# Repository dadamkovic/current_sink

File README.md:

The design is intended to be a programmable current sink controllable manually using an encoder or over USB interface.
It ECU includes:
- 2 parallel separately controlled MOSFETs
- starburst type LCD display with 8 segments + driver IC
- symmetrical power rails +/- 5V
- USB optical isolation protection
- 2 channel DAC
- current monitoring
- optional 'PID' feedback control loop realized using cascaded op-amps 

Current state - HW is finished and a prototype was produced. SW library for control of the display is ready and included in the SW files.

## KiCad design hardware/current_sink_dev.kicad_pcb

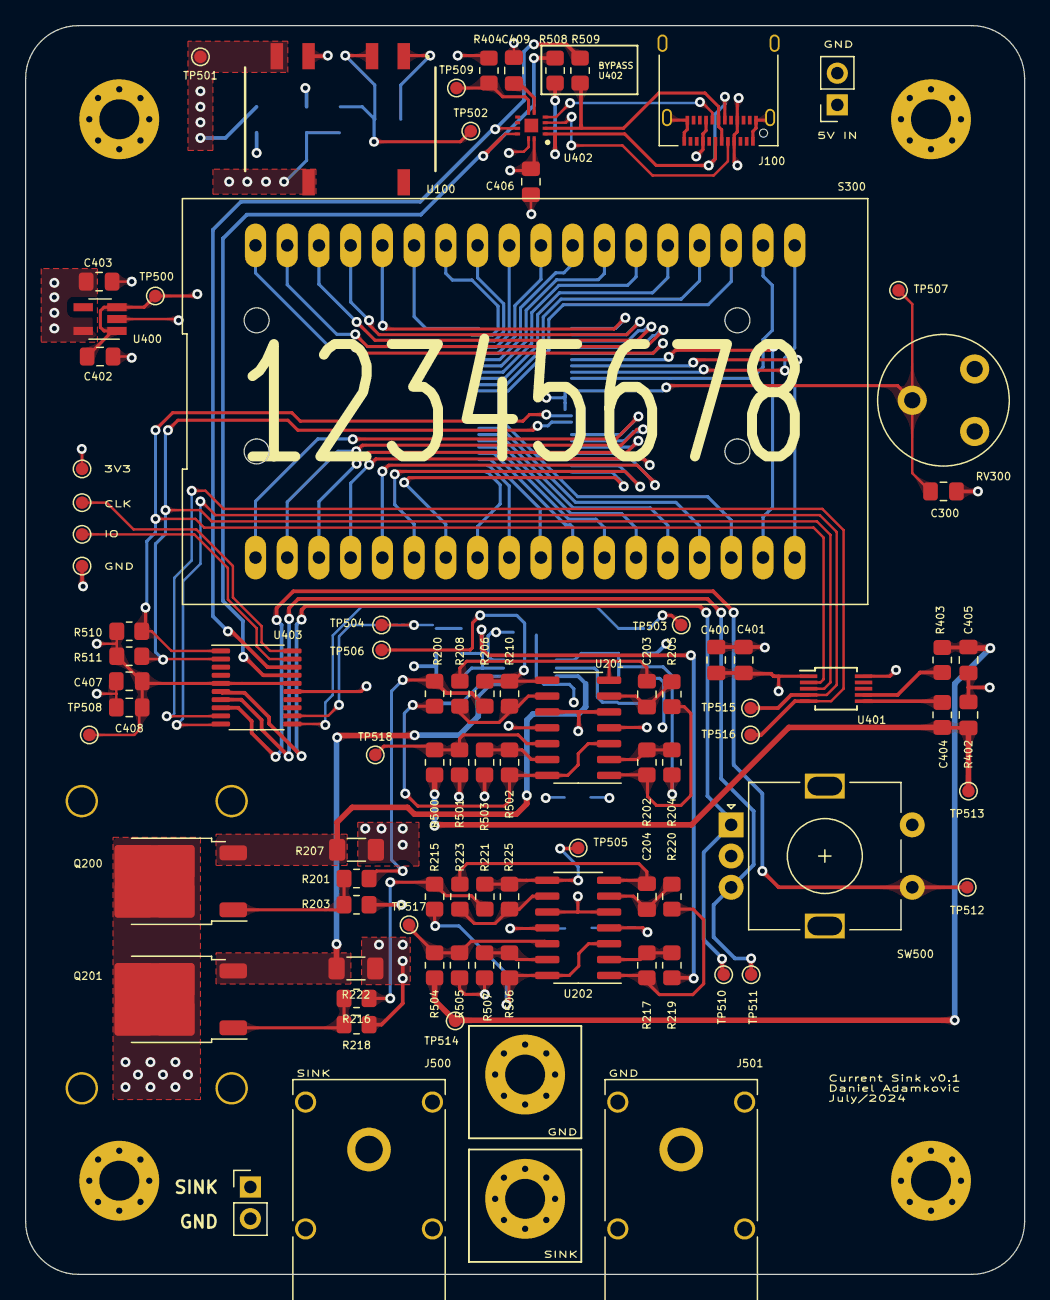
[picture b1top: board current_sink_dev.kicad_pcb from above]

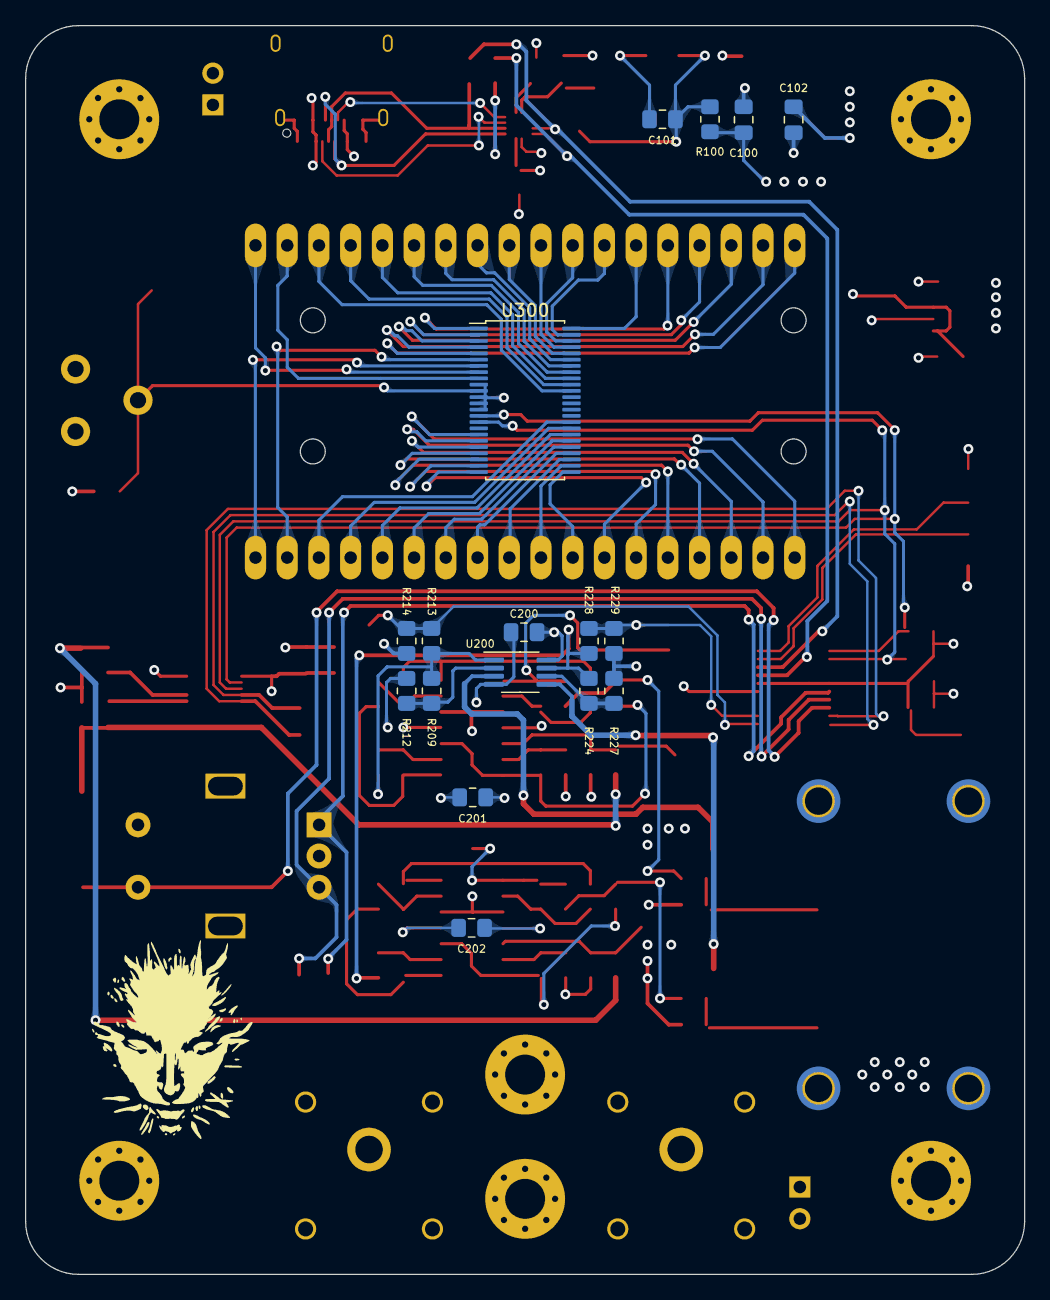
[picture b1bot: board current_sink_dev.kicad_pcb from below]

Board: 4 copper layers, 80.0 x 100.0 mm, 115 parts (21 on the bottom side), 94 nets.

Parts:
C100, C101, C102: 4.7u; C_0805_2012Metric_Pad1.18x1.45mm_HandSolder
C200, C201, C202: ?; C_0805_2012Metric_Pad1.18x1.45mm_HandSolder
C203, C204, C300, C402, C403, C406, C407, C408: 1u; C_0805_2012Metric_Pad1.18x1.45mm_HandSolder
C400, C404, C405, C409: 0.1u; C_0805_2012Metric_Pad1.18x1.45mm_HandSolder
C401: 10u; C_0805_2012Metric_Pad1.18x1.45mm_HandSolder
H500, H501, H502, H503, H504, H505: MountingHole_3.2mm_M3_Pad_Via
H506, H507, H508, H509: MountingHole_2.2mm_M2_ISO7380_Pad_TopOnly
J100: USB_C_Receptacle_USB2.0; USB_C_Receptacle_Amphenol_12401610E4-2A
J500, J501: Conn_01x01_Socket; Banana_Cliff_FCR7350x_S16N-PC_Horizontal
J502: PinHeader_1x02_P2.54mm_Vertical
J503: 5V_IN; PinSocket_1x02_P2.54mm_Vertical
Q200, Q201: TK7S10N1Z; TO-252-2
R100, R500, R501, R504, R505, R508, R509: 0R; R_0805_2012Metric_Pad1.20x1.40mm_HandSolder
R200, R206, R215, R221: 0; R_0805_2012Metric_Pad1.20x1.40mm_HandSolder
R201, R212, R213, R214, R216, R227, R228, R229: 100; R_0805_2012Metric_Pad1.20x1.40mm_HandSolder
R202, R204, R205, R208, R210, R217, R219, R220, R223, R225, R402, R403, R404: 10k; R_0805_2012Metric_Pad1.20x1.40mm_HandSolder
R203, R218: 1k; R_0805_2012Metric_Pad1.20x1.40mm_HandSolder
R207, R222: 100m; R_1206_3216Metric_Pad1.30x1.75mm_HandSolder
R209, R224: 1.9k; R_0805_2012Metric_Pad1.20x1.40mm_HandSolder
R502, R503, R506, R507: R_Small; R_0805_2012Metric_Pad1.20x1.40mm_HandSolder
R510, R511: ?; R_0805_2012Metric_Pad1.20x1.40mm_HandSolder
RV300: PT10LV05; Potentiometer_Piher_PT-10-V05_Vertical
S300: VIM-878-DP-RC-S-LV; VIM878DPRCSLV
SW500: RotaryEncoder_Switch; RotaryEncoder_Alps_EC11E-Switch_Vertical_H20mm
TP500, TP501, TP502, TP503, TP504, TP505, TP506, TP507, TP508, TP509, TP510, TP511, TP512, TP513, TP514, TP515, TP516, TP517, TP518: TestPoint_Pad_D1.0mm
TP519: 3V3; TestPoint_Pad_D1.0mm
TP520: SWDIO; TestPoint_Pad_D1.0mm
TP521: SWDCLK; TestPoint_Pad_D1.0mm
TP522: GND; TestPoint_Pad_D1.0mm
U100: PDSE1-S5-D5-M-TR; PDS1-M
U200: AD8602; MSOP-8_3x3mm_P0.65mm
U201, U202: ADTL084; SOIC-14_3.9x8.7mm_P1.27mm
U300: BU9797A; TSSOP-48_6.1x12.5mm_P0.5mm
U400: MIC5504-1.2YM5; SOT-23-5_HandSoldering
U401: MCP4728; MSOP-10_3x3mm_P0.5mm
U402: DPO2036; UQFN2020-12
U403: STM32F042F6Px; TSSOP-20_4.4x6.5mm_P0.65mm

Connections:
3V3_SUPPLY_G: C400.1, C401.1, C403.1, C406.1, C407.1, C408.1, R404.1, R510.1, R511.1, RV300.3, TP508.1, TP519.1, U400.5 (VOUT), U401.1 (VDD), U402.12 (VSYS), U403.5 (VDDA), U403.16 (VDD)
5V0_SUPPLY_G: C100.1, C200.2, C201.2, C202.2, C402.1, R100.2, TP500.1, U100.7 (+Vout), U200.8 (V+), U201.4 (V+), U202.4 (V+), U400.1 (VIN), U400.3 (EN)
-5V0_SUPPLY_G: C102.2, C200.1, C201.1, C202.1, TP501.1, U100.5 (-Vout), U200.4 (V-), U201.11 (V-), U202.11 (V-)
/LCD_screen/COM0_dig_l: S300.17 (COM0), U300.6 (COM0)
/LCD_screen/COM1_dig_l: S300.18 (COM1), U300.7 (COM1)
/LCD_screen/COM2_dig_l: S300.19 (COM2), U300.8 (COM2)
/LCD_screen/COM3_dig_l: S300.20 (COM3), U300.9 (COM3)
/LCD_screen/disp1_dig_l: S300.1 (PIN1), U300.18 (SEG0)
/LCD_screen/disp2_dig_l: S300.2 (PIN2), U300.19 (SEG1)
/LCD_screen/disp3_dig_l: S300.3 (PIN3), U300.20 (SEG2)
/LCD_screen/disp4_dig_l: S300.4 (PIN4), U300.21 (SEG3)
/LCD_screen/disp5_dig_l: S300.5 (PIN5), U300.22 (SEG4)
/LCD_screen/disp6_dig_l: S300.6 (PIN6), U300.23 (SEG5)
/LCD_screen/disp7_dig_l: S300.7 (PIN7), U300.24 (SEG6)
/LCD_screen/disp8_dig_l: S300.8 (PIN8), U300.25 (SEG7)
/LCD_screen/disp9_dig_l: S300.9 (PIN9), U300.26 (SEG8)
/LCD_screen/disp10_dig_l: S300.10 (PIN10), U300.27 (SEG9)
/LCD_screen/disp11_dig_l: S300.11 (PIN11), U300.28 (SEG10)
/LCD_screen/disp12_dig_l: S300.12 (PIN12), U300.29 (SEG11)
/LCD_screen/disp13_dig_l: S300.13 (PIN13), U300.30 (SEG12)
/LCD_screen/disp14_dig_l: S300.14 (PIN14), U300.31 (SEG13)
/LCD_screen/disp15_dig_l: S300.15 (PIN15), U300.32 (SEG14)
/LCD_screen/disp16_dig_l: S300.16 (PIN16), U300.33 (SEG15)
/LCD_screen/disp21_dig_l: S300.21 (PIN21), U300.38 (SEG20)
/LCD_screen/disp22_dig_l: S300.22 (PIN22), U300.39 (SEG21)
/LCD_screen/disp23_dig_l: S300.23 (PIN23), U300.40 (SEG22)
/LCD_screen/disp24_dig_l: S300.24 (PIN24), U300.41 (SEG23)
/LCD_screen/disp25_dig_l: S300.25 (PIN25), U300.42 (SEG24)
/LCD_screen/disp26_dig_l: S300.26 (PIN26), U300.43 (SEG25)
/LCD_screen/disp27_dig_l: S300.27 (PIN27), U300.44 (SEG26)
/LCD_screen/disp28_dig_l: S300.28 (PIN28), U300.45 (SEG27)
/LCD_screen/disp29_dig_l: S300.29 (PIN29), U300.46 (SEG28)
/LCD_screen/disp30_dig_l: S300.30 (PIN30), U300.47 (SEG29)
/LCD_screen/disp31_dig_l: S300.31 (PIN31), U300.48 (SEG30)
/LCD_screen/disp32_dig_l: S300.32 (PIN32), U300.1 (SEG31)
/LCD_screen/disp33_dig_l: S300.33 (PIN33), U300.2 (SEG32)
/LCD_screen/disp34_dig_l: S300.34 (PIN34), U300.3 (SEG33)
/LCD_screen/disp35_dig_l: S300.35 (PIN35), U300.4 (SEG34)
/LCD_screen/disp36_dig_l: S300.36 (PIN36), U300.5 (SEG35)
/current_sink_stage/current_feedback_A: Q200.3 (S), R207.2, U200.3 (+)
/current_sink_stage/current_feedback_B: Q201.3 (S), R222.2, U200.5 (+)
/supply_gen/usb5v_l: C101.1, J100.A4 (VBUS), J100.A9 (VBUS), J100.B4 (VBUS), J100.B9 (VBUS), J503.1, R100.1, TP502.1, U100.2 (VIN)
/uC_stage/dacNLDAC_dig_l: TP515.1, U401.4 (~LDAC), U403.10 (PA4)
/uC_stage/dacRDY_dig_l: TP516.1, U401.5 (RDY/~BSY), U403.9 (PA3)
/uC_stage/encoderA_dig_l: SW500.A, TP510.1, U403.6 (PA0)
/uC_stage/encoderB_dig_l: SW500.B, TP511.1, U403.7 (PA1)
/uC_stage/encoderSW_dig_l: SW500.S1, TP512.1, U403.8 (PA2)
/uC_stage/swdclk_com_l: TP521.1, U403.20 (PA14)
/uC_stage/swdio_com_l: TP520.1, U403.19 (PA13)
/uC_stage/usbCIsolatorFaultc_dig_l: R404.2, TP509.1, U402.6 (FAULTB)
GND: C100.2, C101.2, C102.1, C300.2, C400.2, C401.2, C402.2, C403.2, C404.2, C405.2, C406.2, C407.2, C408.2, C409.2, H501.1, H502.1, H503.1, H504.1, H505.1, H506.1, H507.1, H508.1, H509.1, J100.A1 (GND), J100.A12 (GND), J100.B1 (GND), J100.B12 (GND), J100.S1 (SHIELD), J501.1, J502.2, J503.2, R203.1, R207.1, R212.1, R214.1, R218.1, R222.1, R227.1, R229.1, R501.2, R503.2, R505.2, R507.2, RV300.1, SW500.C, SW500.S2, TP522.1, U100.1 (GND), U100.4 (0V), U201.5 (+), U201.10 (+), U202.5 (+), U202.10 (+), U300.10 (VLCD), U300.12 (VSS), U300.13 (TEST1), U300.14 (OSCIN), U400.2 (GND), U401.10 (VSS), U402.11 (GND), U403.15 (VSSA)
unnamed: C203.2, R208.2, U201.7
unnamed: C204.2, R223.2, U202.7
unnamed: Q200.1 (G), R201.2, R203.2
unnamed: Q201.1 (G), R216.2, R218.2
unnamed: R200.2, R201.1, R206.2
unnamed: R202.1, R205.2, U201.1
unnamed: R204.2, R209.2, R213.2, U200.1
unnamed: R206.1, R210.2, TP506.1, U201.8
unnamed: R215.2, R216.1, R221.2
unnamed: R217.1, R220.2, U202.1
unnamed: R219.2, R224.2, R228.2, U200.7
unnamed: R221.1, R225.2, TP505.1, U202.8
unnamed: R209.1, R212.2, U200.2 (-)
unnamed: R224.1, R227.2, U200.6 (-)
unnamed: R202.2, R204.1, U201.2 (-)
unnamed: C203.1, R205.1, U201.6 (-)
unnamed: R208.1, R210.1, U201.9 (-)
unnamed: R500.2, R501.1, TP518.1, U201.12 (+)
unnamed: R502.2, R503.1, U201.13 (-)
unnamed: R217.2, R219.1, U202.2 (-)
unnamed: C204.1, R220.1, U202.6 (-)
unnamed: R223.1, R225.1, U202.9 (-)
unnamed: R504.2, R505.1, TP517.1, U202.12 (+)
unnamed: R506.2, R507.1, U202.13 (-)
unnamed: C300.1, RV300.2, TP507.1, U300.11 (VDD)
unnamed: R402.1, U401.6 (VOUTA)
unnamed: R403.2, U401.7 (VOUTB)
unnamed: C409.1, U402.5 (CB)
UCSCL_COM_G: R510.2, U300.15 (SCL), U401.2 (SCL), U403.1 (PB8)
UCSDA_COM_G: R511.2, U300.16 (SDA), U401.3 (SDA), U403.2 (PF0)
USB_C_CC1_G: J100.A5 (CC1), U402.3 (CC1C)
USB_C_CC2_G: J100.B5 (CC2), U402.4 (CC2C)
USB_C_DNEG_G: J100.A7 (D-), J100.B7 (D-), R508.1, U402.1 (SBU1C)
USB_C_DPOS_G: J100.A6 (D+), J100.B6 (D+), R509.2, U402.2 (SBU2C)
USB_C_ISOLATED_DNEG: R508.2, U402.10 (SBUS1S), U403.17 (PA9/PA11)
USB_C_ISOLATED_DPOS: R509.1, U402.9 (SBUS2S), U403.18 (PA10/PA12)
VOLTAGE_SINK_G: H500.1, J500.1, J502.1, Q200.2 (D), Q201.2 (D)
dacOutA_ang_g: C404.1, R402.2, R500.1, TP513.1
dacOutB_ang_g: C405.1, R403.1, R504.1, TP514.1
opStage1A_ang_g: R200.1, R502.1, U201.3 (+), U201.14
opStage1B_ang_g: R215.1, R506.1, U202.3 (+), U202.14
opStage2A_ang_g: R213.1, R214.2, TP503.1, U403.11 (PA5)
opStage2B_ang_g: R228.1, R229.2, TP504.1, U403.12 (PA6)

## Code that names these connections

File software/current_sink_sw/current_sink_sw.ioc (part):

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Mcu.Name=STM32F042F6Px
Mcu.Package=TSSOP20
Mcu.UserName=STM32F042F6Px
PA0.GPIOParameters=GPIO_PuPd,GPIO_Label,GPIO_ModeDefaultEXTI
PA0.GPIO_Label=ENCODER_A
PA0.GPIO_ModeDefaultEXTI=GPIO_MODE_IT_RISING_FALLING
PA0.GPIO_PuPd=GPIO_PULLUP
PA0.Signal=GPXTI0
PA1.GPIOParameters=GPIO_PuPd,GPIO_Label
PA1.GPIO_Label=ENCODER_B
PA1.GPIO_PuPd=GPIO_PULLUP
PA1.Signal=GPIO_Input
PA13.Mode=Serial_Wire
PA13.Signal=SYS_SWDIO
PA14.Mode=Serial_Wire
PA14.Signal=SYS_SWCLK
PA2.GPIOParameters=GPIO_PuPd,GPIO_Label,GPIO_ModeDefaultEXTI
PA2.GPIO_Label=ENCODER_SW
PA2.GPIO_ModeDefaultEXTI=GPIO_MODE_IT_FALLING
PA2.GPIO_PuPd=GPIO_PULLUP
PA2.Signal=GPXTI2
PA3.GPIOParameters=GPIO_PuPd,GPIO_Label
PA3.GPIO_Label=RDY
PA3.GPIO_PuPd=GPIO_PULLUP
PA3.Signal=GPIO_Input
PA4.GPIOParameters=GPIO_Label
PA4.GPIO_Label=NLDAC
PA4.Signal=GPIO_Output
PA5.GPIOParameters=GPIO_Label
PA5.GPIO_Label=CHANNEL_B_CURR
PA5.Mode=IN5
PA5.Signal=ADC_IN5
PA6.GPIOParameters=GPIO_Label
PA6.GPIO_Label=CHANNEL_A_CURR
PA6.Mode=IN6
PA6.Signal=ADC_IN6
PB8.GPIOParameters=GPIO_Pu
PB8.GPIO_Pu=GPIO_PULLUP
PB8.Mode=I2C
PB8.Signal=I2C1_SCL
PF0-OSC_IN.GPIOParameters=GPIO_Pu
PF0-OSC_IN.GPIO_Pu=GPIO_PULLUP
PF0-OSC_IN.Mode=I2C
PF0-OSC_IN.Signal=I2C1_SDA
board=custom

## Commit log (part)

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2024-02-18 Initial commit. Started work on schematic.
2024-02-27 Updates to structure of the schematic. Minor funcitonality adjustments.
2024-03-03 Began initial routing. Schematic still not fully complete.
2024-03-09 Changed to 4 layer design.
2024-03-17 Routing close to completion. Pending review.
2025-03-23 Started programming LCD interface
2025-03-24 Started work on register setting for MCP
2025-03-26 Changed CMake .vscode files to allow flashing and debugging. Created first somewhat functional library.
2025-03-26 First working version of library for writing numbers. Requires cleanup.
2025-04-06 Added some doucmentation to MCP driver
2025-04-07 Started work on task manager
